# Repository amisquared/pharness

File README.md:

# pharness

phone-necromancy platform 😨

## what does it do?
it powers any phone that takes 4.8v, from usb-pd which negotiates 9v@2a, and then stepped down to 4.8v@2a

it is also partially inspired by postmarketOS' phone harness for their hwci project.

## license
this project is licensed under [CERN-OHL-P](https://ohwr.org/cern_ohl_p_v2.txt)

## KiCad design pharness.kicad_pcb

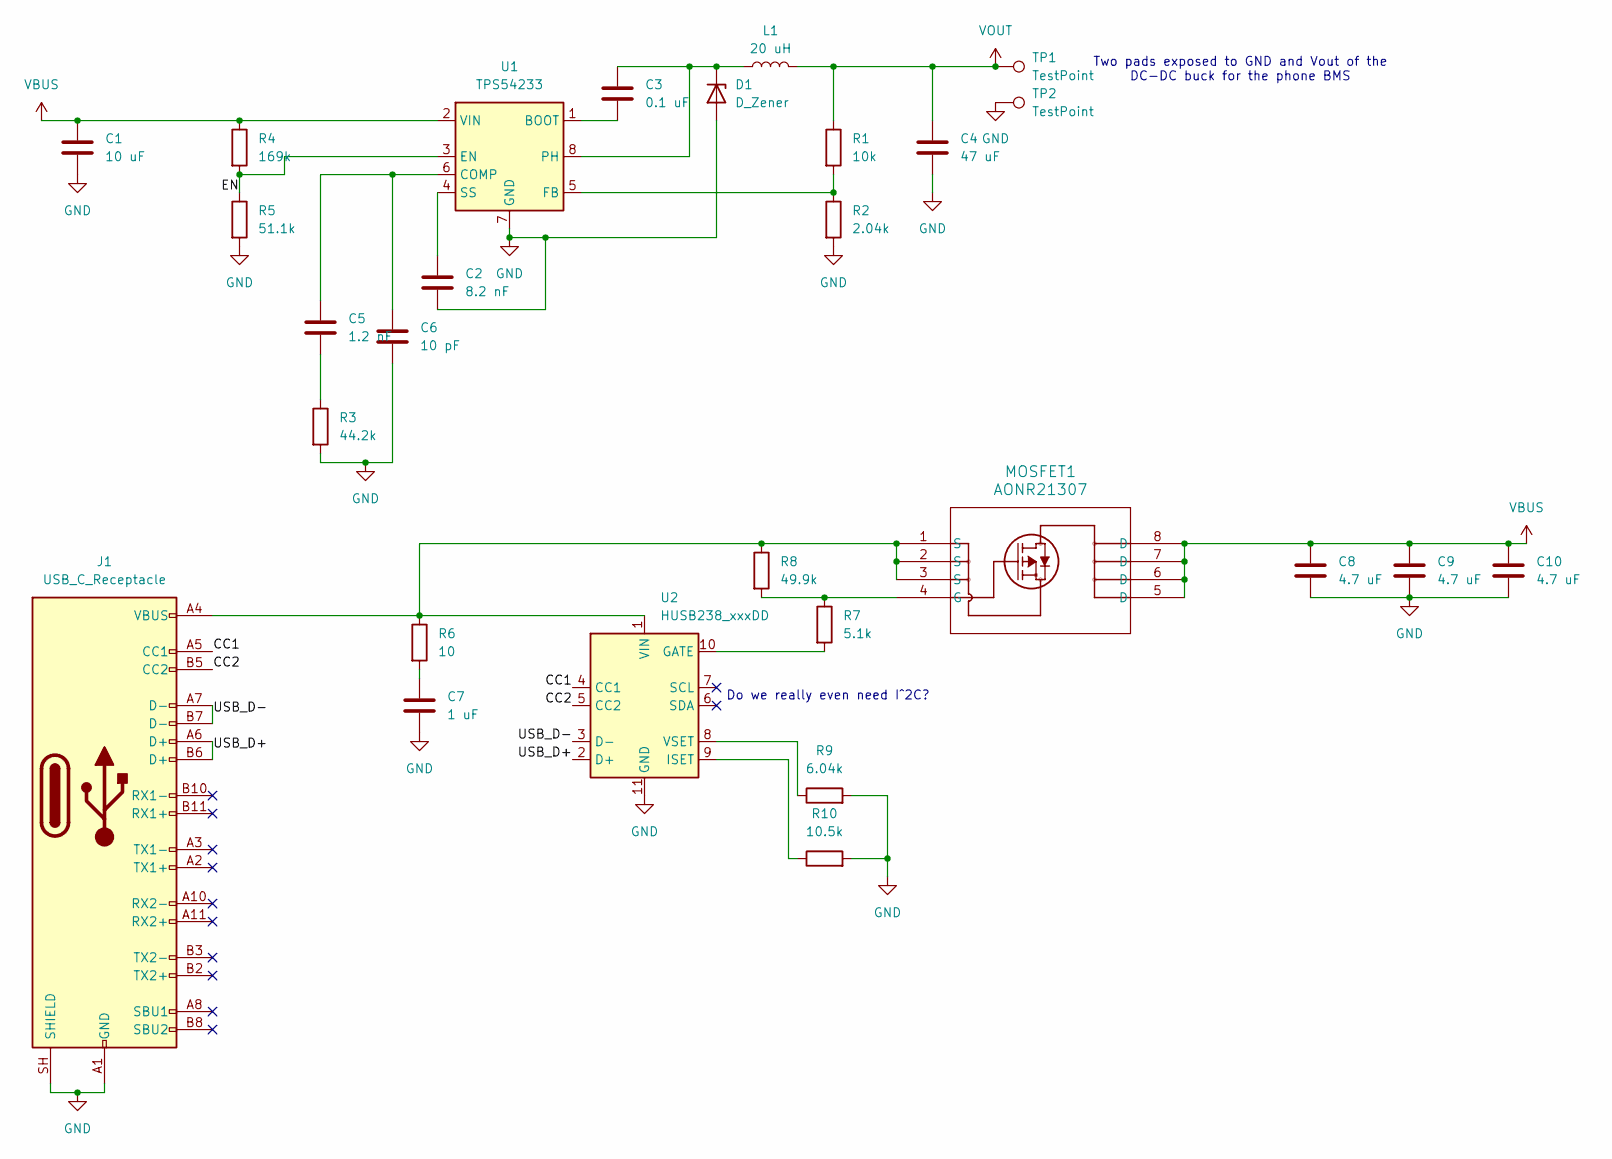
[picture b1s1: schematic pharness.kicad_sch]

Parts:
C1: 10 uF; C_0805_2012Metric_Pad1.18x1.45mm_HandSolder
C2: 8.2 nF; C_0805_2012Metric_Pad1.18x1.45mm_HandSolder
C3: 0.1 uF; C_0805_2012Metric_Pad1.18x1.45mm_HandSolder
C4: 47 uF; C_0805_2012Metric_Pad1.18x1.45mm_HandSolder
C5: 1.2 nF; C_0805_2012Metric_Pad1.18x1.45mm_HandSolder
C6: 10 pF; C_0805_2012Metric_Pad1.18x1.45mm_HandSolder
C7: 1 uF; C_0805_2012Metric_Pad1.18x1.45mm_HandSolder
C8, C9, C10: 4.7 uF; C_0805_2012Metric_Pad1.18x1.45mm_HandSolder
D1: D_Zener; D_SOD-323_HandSoldering
J1: USB_C_Receptacle; USB_C_Receptacle_JAE_DX07S016JA1R1500
L1: 20 uH; L_1206_3216Metric_Pad1.22x1.90mm_HandSolder
MOSFET1: AONR21307; DFN8_3x3_EP_AOS
R1: 10k; R_0805_2012Metric_Pad1.20x1.40mm_HandSolder
R2: 2.04k; R_0805_2012Metric_Pad1.20x1.40mm_HandSolder
R3: 44.2k; R_0805_2012Metric_Pad1.20x1.40mm_HandSolder
R4: 169k; R_0805_2012Metric_Pad1.20x1.40mm_HandSolder
R5: 51.1k; R_0805_2012Metric_Pad1.20x1.40mm_HandSolder
R6: 10; R_0805_2012Metric_Pad1.20x1.40mm_HandSolder
R7: 5.1k; R_0805_2012Metric_Pad1.20x1.40mm_HandSolder
R8: 49.9k; R_0805_2012Metric_Pad1.20x1.40mm_HandSolder
R9: 6.04k; R_0805_2012Metric_Pad1.20x1.40mm_HandSolder
R10: 10.5k; R_0805_2012Metric_Pad1.20x1.40mm_HandSolder
TP1, TP2: TestPoint; TestPoint_Pad_4.0x4.0mm
U1: TPS54233; SOIC-8_3.9x4.9mm_P1.27mm
U2: HUSB238_xxxDD; WDFN-10-1EP_3x3mm_P0.5mm_EP1.8x2.5mm

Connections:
/CC1: J1.A5 (CC1), U2.4 (CC1)
/CC2: J1.B5 (CC2), U2.5 (CC2)
/EN: R4.2, R5.1, U1.3 (EN)
/USB_D+: J1.A6 (D+), J1.B6 (D+), U2.2 (D+)
/USB_D-: J1.A7 (D-), J1.B7 (D-), U2.3 (D-)
GND: C1.2, C2.2, C4.2, C6.2, C7.2, C8.2, C9.2, C10.2, D1.2 (A), J1.A1 (GND), J1.A12 (GND), J1.B1 (GND), J1.B12 (GND), J1.SH (SHIELD), R2.2, R3.2, R5.2, R9.2, R10.2, TP2.1 (1_1), U1.7 (GND), U2.11 (GND)
unnamed: C5.2, R3.1
unnamed: C7.1, R6.2
unnamed: C3.1, D1.1 (K), L1.1, U1.8 (PH)
unnamed: MOSFET1.4 (G), R7.1, R8.2
unnamed: C3.2, U1.1 (BOOT)
unnamed: C5.1, C6.1, U1.6 (COMP)
unnamed: R1.2, R2.1, U1.5 (FB)
unnamed: C2.1, U1.4 (SS)
unnamed: R7.2, U2.10 (GATE)
unnamed: R10.1, U2.9 (ISET)
unnamed: J1.A4 (VBUS), J1.A9 (VBUS), J1.B4 (VBUS), J1.B9 (VBUS), MOSFET1.1 (S), MOSFET1.2 (S), MOSFET1.3 (S), R6.1, R8.1, U2.1 (VIN)
unnamed: R9.1, U2.8 (VSET)
VBUS: C1.1, C8.1, C9.1, C10.1, MOSFET1.5 (D), MOSFET1.6 (D), MOSFET1.7 (D), MOSFET1.8 (D), MOSFET1.9, R4.1, U1.2 (VIN)
VOUT: C4.1, L1.2, R1.1, TP1.1 (1_1)

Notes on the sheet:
Two pads exposed to GND and Vout of the DC-DC buck for the phone BMS
Do we really even need I^2C?

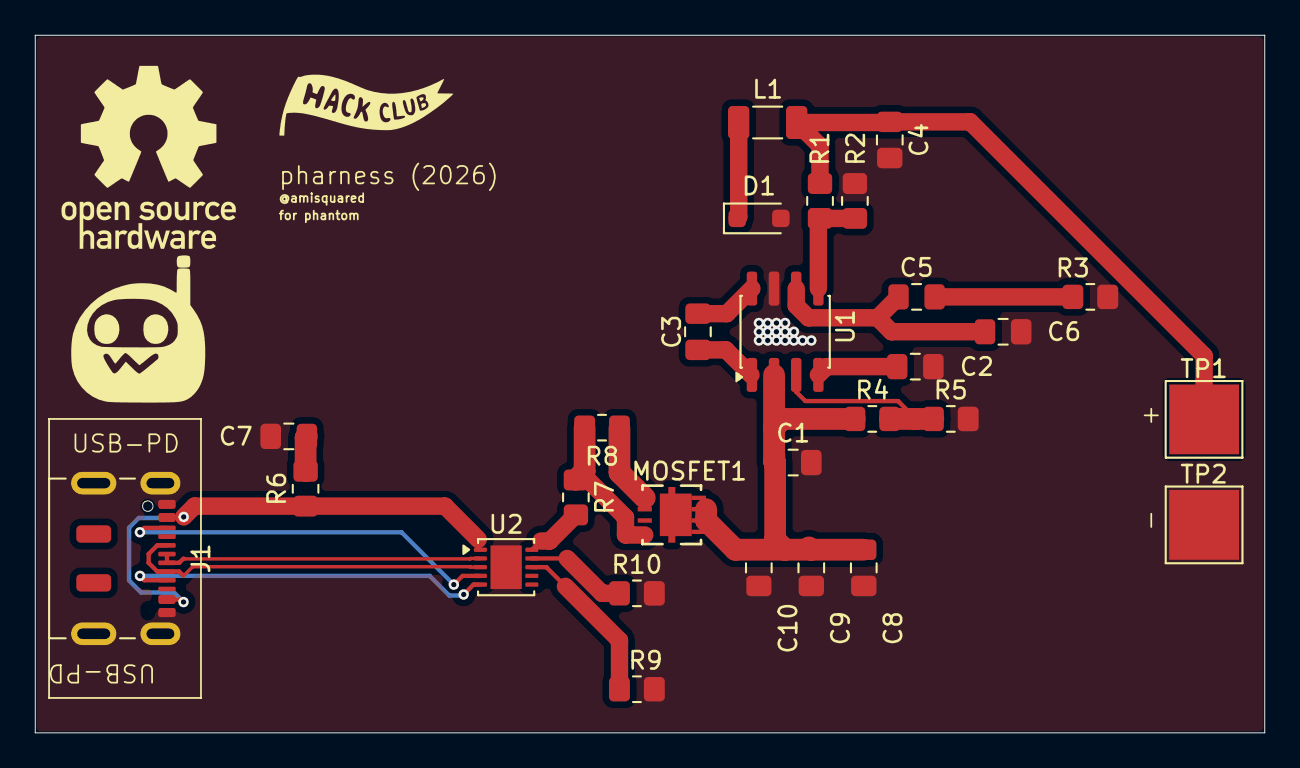
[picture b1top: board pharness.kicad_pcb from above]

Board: 2 copper layers, 70.5 x 40.0 mm, 28 parts (0 on the bottom side), 20 nets.
